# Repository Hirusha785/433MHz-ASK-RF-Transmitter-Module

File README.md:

# 📡 433MHz ASK RF Transmitter Module

## 🚀 Overview

**433MHz ASK RF Transmitter Module** is a compact open-hardware wireless transmitter PCB designed for sending **433MHz Amplitude Shift Keying signals** from microcontrollers and embedded systems.

This project includes a custom schematic, PCB layout, RF coil antenna section, transistor-based RF stage, LC tuning network, and simple 3-pin interface for easy integration with Arduino, ESP32, STM32, Raspberry Pi Pico, and other embedded platforms.

The module is suitable for RF learning, short-range wireless communication, remote-control experiments, sensor transmitters, IoT nodes, and custom embedded hardware projects.

---

## ✨ Key Features

- 📡 **433MHz RF transmission**
- 📶 **ASK modulation**
- 🔌 **Simple 3-pin interface: VCC, DATA, GND**
- ⚡ **Transistor-based RF driver stage**
- 🧲 **LC tuning network**
- 🔁 **Microcontroller-controlled data transmission**
- 📻 **Helical antenna support**
- 🧩 **Compact PCB layout**
- 🛠️ **Open-hardware design**
- 🧪 **Useful for RF testing, learning, and prototyping**

---

## 🧠 Technical Description

This module is designed to transmit digital data using **Amplitude Shift Keying** at approximately **433MHz**.

A microcontroller sends a digital signal to the **DATA** pin. This signal controls the transmitter stage and modulates the RF carrier amplitude. The RF signal is generated and shaped using transistor stages, coils, capacitors, and a frequency reference section.

The output is transmitted through the antenna section, which can use a helical antenna or a properly sized wire antenna depending on range and space requirements.

---

## 🧱 System Block Diagram

```text
Microcontroller GPIO
        ↓
DATA Input
        ↓
ASK Modulation Stage
        ↓
RF Oscillator / Frequency Reference
        ↓
Transistor RF Driver Stage
        ↓
LC Tuning Network
        ↓
Antenna Output
        ↓
433MHz Wireless Transmission
```

---

## 🔌 Pinout

| Pin | Name | Description |
|---|---|---|
| 1 | VCC | Power input |
| 2 | DATA | ASK data input from microcontroller |
| 3 | GND | Ground connection |

---

## 🧩 Main Components

| Component | Value / Type | Function |
|---|---|---|
| AE1 | Antenna | Transmits the 433MHz RF signal |
| L1 | 8 turns | RF tuning / oscillator coil |
| L2 | 3 turns | Antenna coupling / RF output coil |
| C1 | 7pF | RF tuning capacitor |
| C2 | 7pF | Antenna coupling capacitor |
| R1 | 27kΩ | Biasing resistor |
| R2 | 27kΩ | DATA input / modulation resistor |
| Q1 | 2SC4213 | RF transistor stage |
| Q2 | 2SC4213 | Modulation / RF driver transistor stage |
| Y1 | Crystal / Resonator | Frequency reference component |
| J1 | 3-pin connector | VCC, DATA, GND interface |

---

## ⚙️ Hardware Design Sections

### 1. Power Input Section

The module receives power through the **VCC** and **GND** pins.

A stable power supply is important because RF output strength and frequency stability can be affected by voltage noise or weak supply current.

---

### 2. DATA Input Section

The **DATA** pin receives a digital signal from a microcontroller.

Typical connection:

```text
Microcontroller VCC   →  VCC
Microcontroller GPIO  →  DATA
Microcontroller GND   →  GND
```

The DATA input controls the ASK modulation behavior of the transmitter.

---

### 3. RF Oscillator Section

The oscillator section generates the RF carrier signal around the 433MHz band.

The frequency reference component, transistor stage, coils, and capacitors help form the RF signal generation network.

---

### 4. ASK Modulation Section

ASK means **Amplitude Shift Keying**.

In this module, the input data changes the amplitude of the RF signal.  
When the DATA signal changes between HIGH and LOW states, the RF output amplitude changes accordingly.

---

### 5. RF Driver Stage

The transistor-based RF stage helps drive the RF signal toward the antenna section.

This stage is important for signal strength and transmission range.

---

### 6. Antenna Output Section

The antenna section radiates the 433MHz RF signal.

A properly designed antenna improves:

- Transmission distance
- Signal stability
- RF efficiency
- Receiver detection quality

---

## 🧪 Testing Methods

You can test this transmitter module using:

- Arduino
- ESP32
- STM32
- Raspberry Pi Pico
- Oscilloscope
- SDR receiver
- 433MHz ASK receiver module
- Logic analyzer
- RF spectrum analyzer

Example testing flow:

```text
Microcontroller
      ↓
433MHz ASK Transmitter Module
      ↓
Wireless RF Signal
      ↓
433MHz ASK Receiver Module
      ↓
Microcontroller / Logic Analyzer
```

---

## 🧑‍💻 Arduino Basic ASK Transmit Code

```cpp
#define TX_DATA_PIN 2

const unsigned int BIT_DELAY_US = 500;

void sendBit(bool bitValue) {
  digitalWrite(TX_DATA_PIN, bitValue ? HIGH : LOW);
  delayMicroseconds(BIT_DELAY_US);
}

void sendByte(byte data) {
  for (int i = 7; i >= 0; i--) {
    sendBit((data >> i) & 0x01);
  }
}

void sendFrame(byte payload) {
  // Preamble for receiver synchronization
  for (int i = 0; i < 8; i++) {
    sendByte(0xAA);
  }

  // Sync bytes
  sendByte(0x2D);
  sendByte(0xD4);

  // Payload
  sendByte(payload);

  // Simple inverted payload for basic checking
  sendByte(~payload);

  // Stop transmission
  digitalWrite(TX_DATA_PIN, LOW);
}

void setup() {
  pinMode(TX_DATA_PIN, OUTPUT);
  digitalWrite(TX_DATA_PIN, LOW);
}

void loop() {
  static byte counter = 0;

  sendFrame(counter);
  counter++;

  delay(1000);
}
```

---

## 🧑‍💻 ESP32 Basic ASK Transmit Code

```cpp
#define TX_DATA_PIN 27

const unsigned int BIT_DELAY_US = 500;

void sendBit(bool bitValue) {
  digitalWrite(TX_DATA_PIN, bitValue ? HIGH : LOW);
  delayMicroseconds(BIT_DELAY_US);
}

void sendByte(uint8_t data) {
  for (int i = 7; i >= 0; i--) {
    sendBit((data >> i) & 0x01);
  }
}

void sendFrame(uint8_t payload) {
  // Preamble for receiver synchronization
  for (int i = 0; i < 8; i++) {
    sendByte(0xAA);
  }

  // Sync bytes
  sendByte(0x2D);
  sendByte(0xD4);

  // Payload
  sendByte(payload);

  // Simple inverted payload for basic checking
  sendByte(~payload);

  // Stop transmission
  digitalWrite(TX_DATA_PIN, LOW);
}

void setup() {
  pinMode(TX_DATA_PIN, OUTPUT);
  digitalWrite(TX_DATA_PIN, LOW);
}

void loop() {
  static uint8_t counter = 0;

  sendFrame(counter);
  counter++;

  delay(1000);
}
```

---

## 🔬 Oscilloscope / RF Testing

Recommended testing points:

| Test Point | Purpose |
|---|---|
| DATA pin | Check microcontroller input waveform |
| Q2 stage | Check modulation switching behavior |
| Oscillator section | Verify RF activity |
| Antenna output | Check transmitted RF signal |
| Receiver output | Confirm wireless transmission |

---

## 🖼️ Project Preview

### Schematic

### PCB Layout

### 3D View

---

## 🛠️ PCB Design Notes

- Keep the antenna trace short and clean.
- Keep RF traces away from noisy digital signals.
- Use a stable ground reference around the RF section.
- Place RF tuning components close to the transistor RF stage.
- Avoid unnecessary long traces in the oscillator section.
- Keep the DATA input trace away from the antenna path where possible.
- Use short routing between the LC network and antenna output.
- Avoid sharp corners in RF traces.
- Test the transmitter with a receiver or SDR before final production.
- RF performance depends heavily on antenna design, PCB layout, supply voltage, and component tolerance.

---

## 📡 Antenna Notes

For 433MHz, a common quarter-wave wire antenna length is approximately:

```text
17.3 cm
```

A helical antenna can also be used for compact designs.

The final range depends on:

- Antenna type
- Antenna tuning
- Supply voltage
- PCB layout
- Receiver sensitivity
- Environmental interference
- Distance and obstacles

---

## ⚠️ Important Notes

This project is intended for:

- Educational use
- RF learning
- Embedded hardware experiments
- Short-range wireless prototyping
- ASK transmitter testing

RF transmission is regulated in many countries.  
Before commercial or public deployment, make sure the design follows local RF regulations, frequency limits, duty-cycle limits, and output power limits.

---

## 👨‍💻 Author

Designed by **Fernando S.M.H.G**

Open-hardware RF transmitter project for embedded systems, electronics learning, RF experimentation, and wireless communication projects.

---

## 📜 License

This project is released under the **MIT License**.

You are free to use, modify, improve, and share this project with proper attribution.

---

## ⭐ Support

If this project helps you, consider giving the repository a star.

```text
Made for RF learning, embedded systems, and open-hardware development.
```
````

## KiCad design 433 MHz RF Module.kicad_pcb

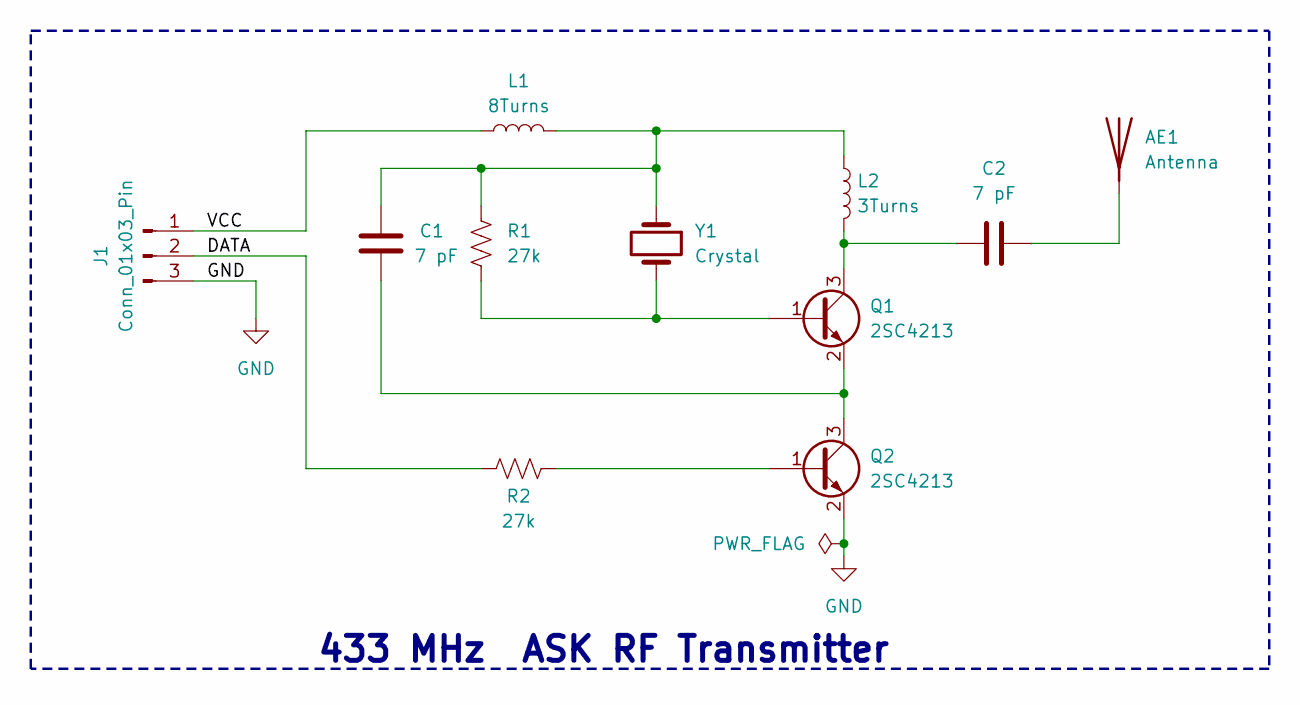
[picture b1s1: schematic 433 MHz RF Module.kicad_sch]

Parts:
AE1: Antenna; NiceRF_SW868-TH13_868Mhz
C1, C2: 7 pF; C_1206_3216Metric
J1: Conn_01x03_Pin; PinHeader_1x03_P2.54mm_Horizontal
L1: 8Turns; L_Axial_L7.0mm_D3.3mm_P12.70mm_Horizontal_Fastron_MICC
L2: 3Turns; L_Axial_L5.3mm_D2.2mm_P7.62mm_Horizontal_Vishay_IM-1
Q1, Q2: 2SC4213; SOT-323_SC-70
R1, R2: 27k; R_0805_2012Metric
Y1: Crystal; Crystal_HC52-6mm_Horizontal

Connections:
/DATA: J1.2, R2.1
/VCC: J1.1, L1.1
GND: J1.3, Q2.2 (E)
unnamed 3: AE1.1, C2.2; also elsewhere on the board
unnamed: C1.1, L1.2, L2.1, R1.1, Y1.1
unnamed: Q1.1 (B), R1.2, Y1.2
unnamed: C2.1, L2.2, Q1.3 (C)
unnamed: C1.2, Q1.2 (E), Q2.3 (C)
unnamed: Q2.1 (B), R2.2

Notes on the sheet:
433 MHz ASK RF Transmitter

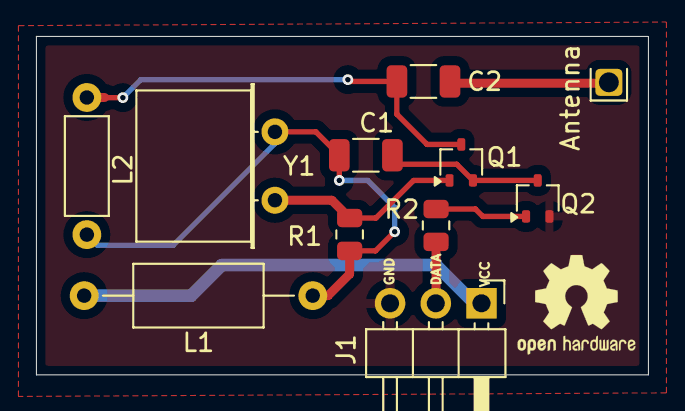
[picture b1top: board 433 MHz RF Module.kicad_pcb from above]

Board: 2 copper layers, 34.0 x 18.8 mm, 11 parts (0 on the bottom side), 9 nets.

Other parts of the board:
Antenna: Antenna; NiceRF_SW868-TH13_868Mhz

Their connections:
unnamed 3: Antenna.1 (A); also elsewhere on the board

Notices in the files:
README.md:
License: MIT
